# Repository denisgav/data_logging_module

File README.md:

Board connects SD Card, RTC and BME sensors.
Can be used to measeure temperature, hummidity and pressure.
SD card can be used to lod the data.

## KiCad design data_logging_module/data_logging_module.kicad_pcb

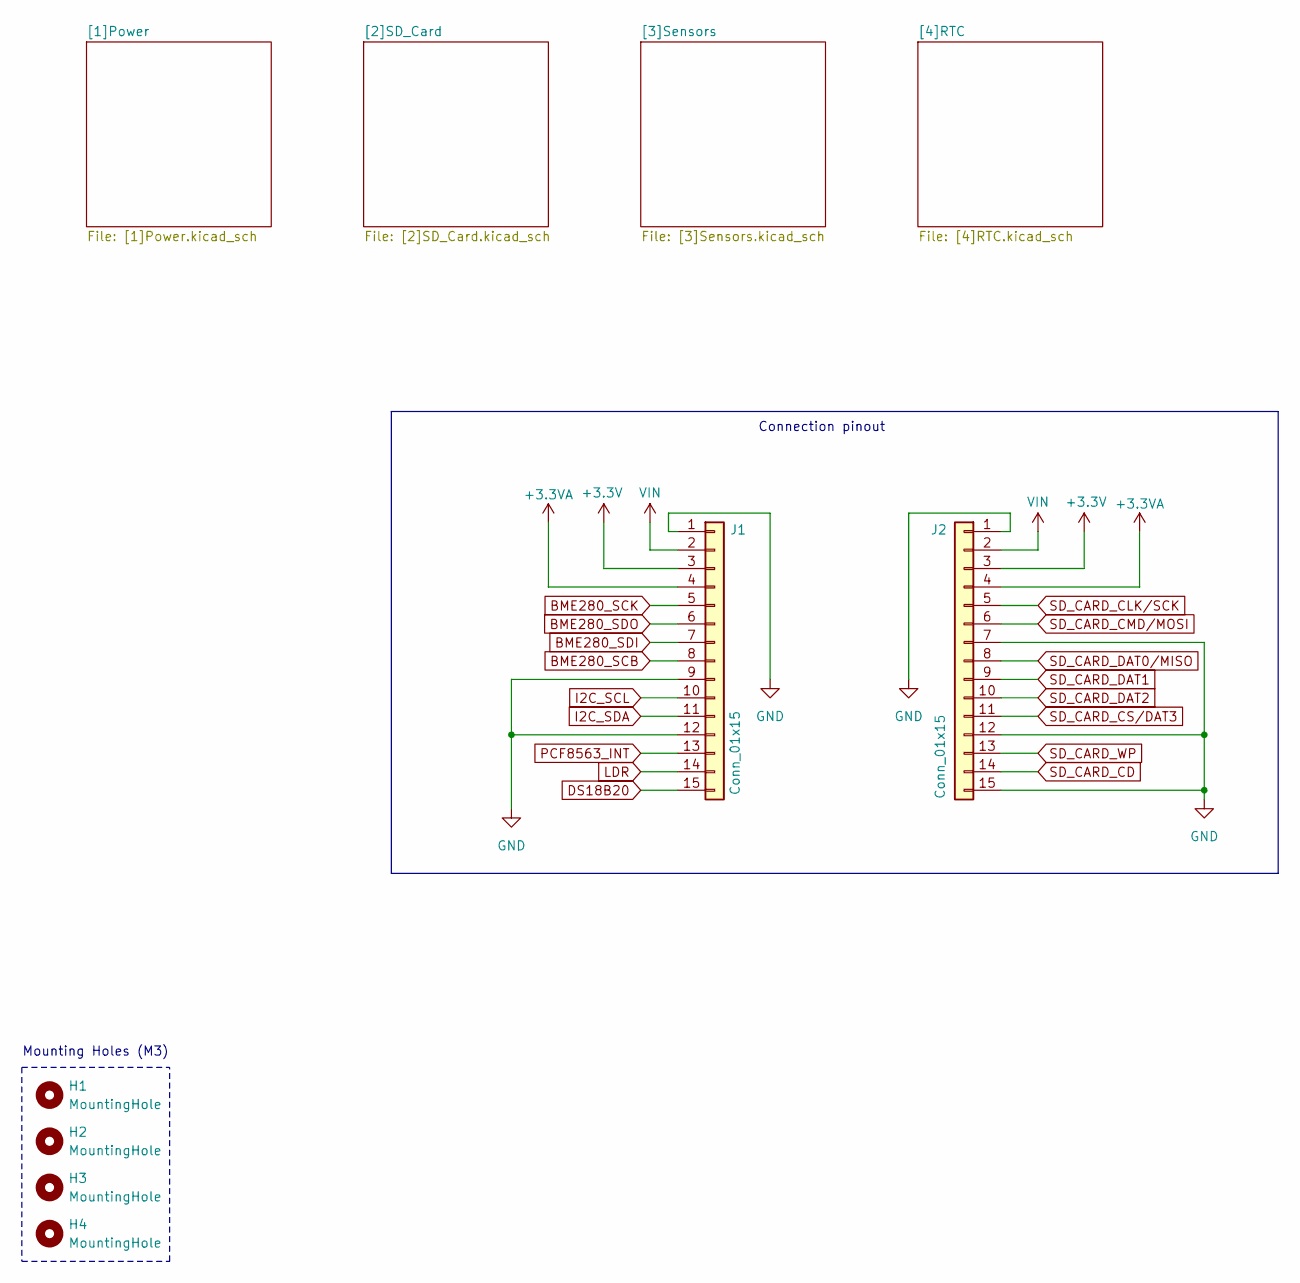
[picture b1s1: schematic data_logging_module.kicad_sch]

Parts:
H1, H2, H3, H4: MountingHole; MountingHole_3.2mm_M3
J1, J2: Conn_01x15; PinSocket_1x15_P2.54mm_Vertical

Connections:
+3.3V: J1.3, J2.3; also elsewhere on the board
+3.3VA: J1.4, J2.4; also elsewhere on the board
BME280_SCB: J1.8; also elsewhere on the board
BME280_SCK: J1.5; also elsewhere on the board
BME280_SDI: J1.7; also elsewhere on the board
BME280_SDO: J1.6; also elsewhere on the board
DS18B20: J1.15; also elsewhere on the board
GND: J1.1, J1.9, J1.12, J2.1, J2.7, J2.12, J2.15; also elsewhere on the board
I2C_SCL: J1.10; also elsewhere on the board
I2C_SDA: J1.11; also elsewhere on the board
LDR: J1.14; also elsewhere on the board
PCF8563_INT: J1.13; also elsewhere on the board
SD_CARD_CD: J2.14; also elsewhere on the board
SD_CARD_CLK/SCK: J2.5; also elsewhere on the board
SD_CARD_CMD/MOSI: J2.6; also elsewhere on the board
SD_CARD_CS/DAT3: J2.11; also elsewhere on the board
SD_CARD_DAT0/MISO: J2.8; also elsewhere on the board
SD_CARD_DAT1: J2.9; also elsewhere on the board
SD_CARD_DAT2: J2.10; also elsewhere on the board
SD_CARD_WP: J2.13; also elsewhere on the board
VIN: J1.2, J2.2; also elsewhere on the board

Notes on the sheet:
Mounting Holes (M3)
Connection pinout

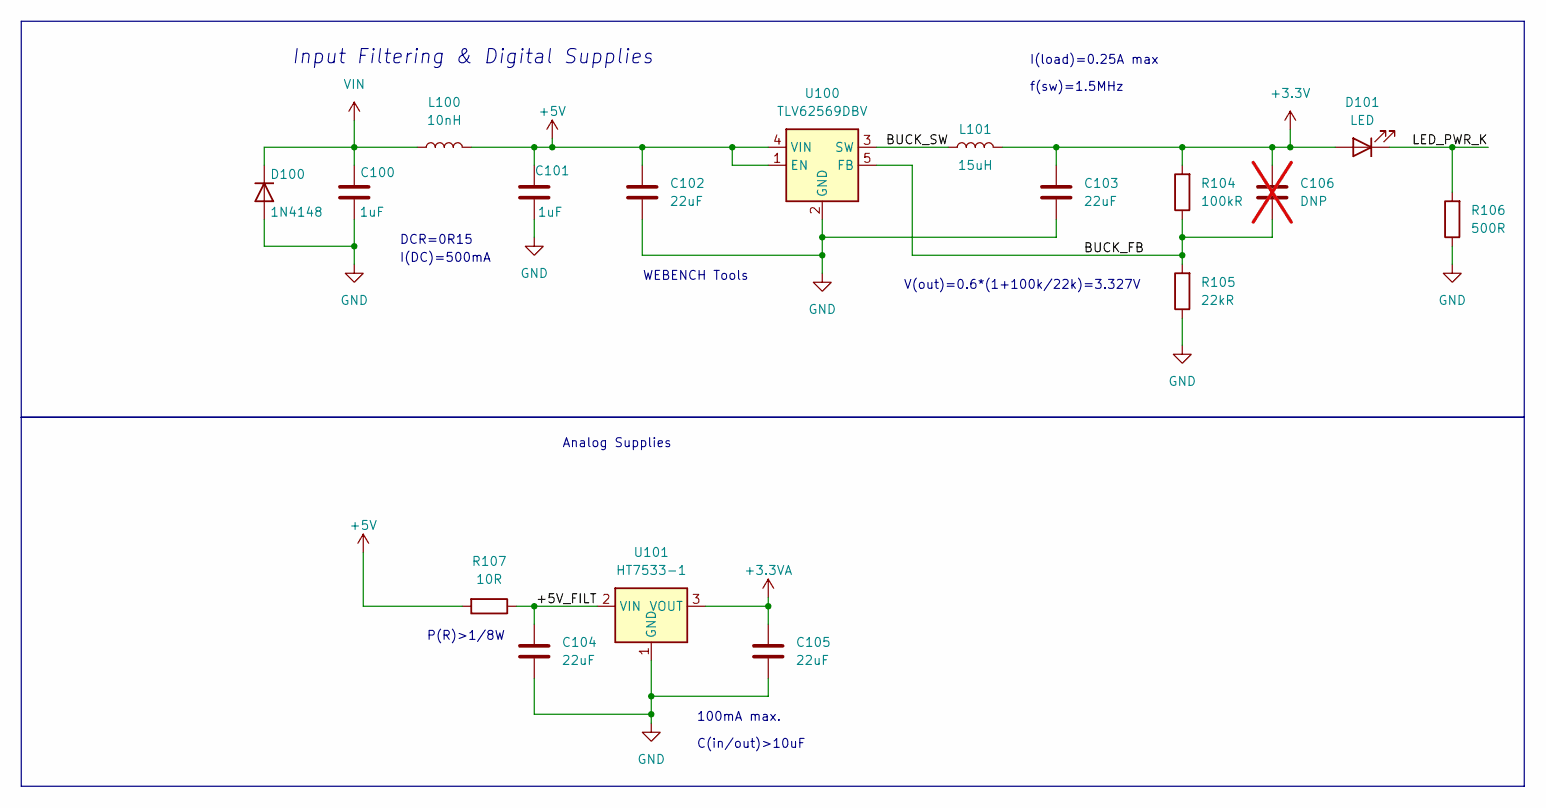
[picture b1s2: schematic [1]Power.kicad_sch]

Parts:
C100, C101: 1uF; C_0805_2012Metric; Manufacturer Part Number CL21B105KBFNNNE; DigiKey Part Number 1276-1946-6-ND
C102, C103: 22uF; C_0805_2012Metric; Manufacturer Part Number CL21A226MAYNNNE; DigiKey Part Number 1276-6687-6-ND
C104, C105: 22uF; C_0805_2012Metric; Manufacturer Part Number CL21A226MAYNNNE
C106: DNP; C_0603_1608Metric; not fitted
D100: 1N4148; D_SOD-123; Manufacturer Part Number 1N4148W
D101: LED; LED_D5.0mm; DigiKey Part Number 732-4971-6-ND
L100: 10nH; L_0603_1608Metric; Manufacturer Part Number LQG18HN10NJ00D; DigiKey Part Number 712-LRC0402CJ10NGV001TDKR-ND
L101: 15uH; MWSA0603S; Manufacturer Part Number FXL0630-150-M; DigiKey Part Number 3442-MWSA0603S-150MTDKR-ND
R104: 100kR; R_0805_2012Metric; Manufacturer Part Number 0805W8F1003T5E; DigiKey Part Number P100KLDKR-ND
R105: 22kR; R_0805_2012Metric; Manufacturer Part Number 0805W8F2202T5E; DigiKey Part Number P22.0KLDKR-ND
R106: 500R; R_0805_2012Metric; Manufacturer Part Number ARG05FTC5000; DigiKey Part Number P1.00KLDKR-ND
R107: 10R; R_0805_2012Metric; Manufacturer Part Number 0805W8F100JT5E
U100: TLV62569DBV; SOT-23-5; Manufacturer Part Number TLV62569DBVR; DigiKey Part Number 296-47360-6-ND
U101: HT7533-1; SOT-89-3; Manufacturer Part Number HT7533-1

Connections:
+3.3V: C103.1, C106.1, D101.2 (A), L101.2, R104.2; also elsewhere on the board
+3.3VA: C105.1, U101.3 (VOUT); also elsewhere on the board
+5V: C101.1, C102.1, L100.2, R107.2, U100.1 (EN), U100.4 (VIN)
/[1]Power/+5V_FILT: C104.1, R107.1, U101.2 (VIN)
/[1]Power/BUCK_FB: C106.2, R104.1, R105.2, U100.5 (FB)
/[1]Power/BUCK_SW: L101.1, U100.3 (SW)
/[1]Power/LED_PWR_K: D101.1 (K), R106.2
GND: C100.2, C101.2, C102.2, C103.2, C104.2, C105.2, D100.2 (A), R105.1, R106.1, U100.2 (GND), U101.1 (GND); also elsewhere on the board
VIN: C100.1, D100.1 (K), L100.1; also elsewhere on the board

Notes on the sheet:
Input Filtering & Digital Supplies
V(out)=0.6*(1+100k/22k)=3.327V
I(DC)=500mA
Analog Supplies
WEBENCH Tools
100mA max.
I(load)=0.25A max
P(R)>1/8W
DCR=0R15
C(in/out)>10uF
f(sw)=1.5MHz

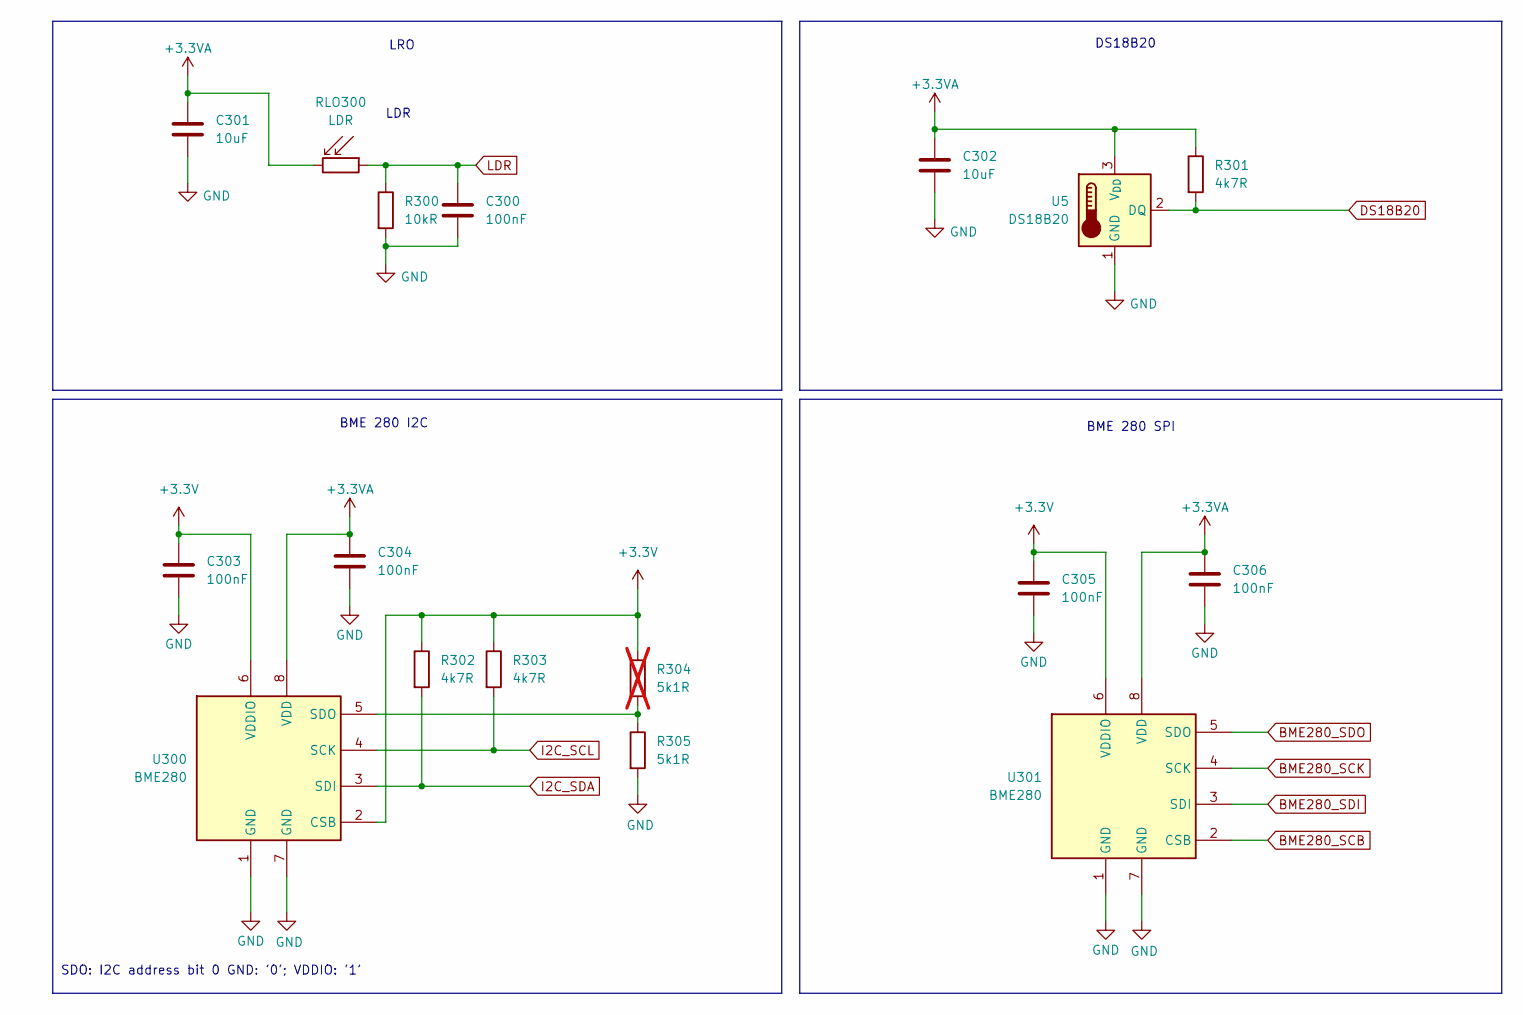
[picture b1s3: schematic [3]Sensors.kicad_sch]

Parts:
C300, C303, C304, C305, C306: 100nF; C_0603_1608Metric; Manufacturer Part Number CL10B104KB8NNNC
C301, C302: 10uF; C_0805_2012Metric; Manufacturer Part Number CL21A106KOQNNNE
R300: 10kR; R_0805_2012Metric; Manufacturer Part Number 0805W8F1002T5E
R301, R302, R303: 4k7R; R_0805_2012Metric; Manufacturer Part Number 0805W8F4701T5E
R304: 5k1R; R_0805_2012Metric; Manufacturer Part Number 0805W8F5101T5E; not fitted
R305: 5k1R; R_0805_2012Metric; Manufacturer Part Number 0805W8F5101T5E
RLO300: LDR; R_LDR_5.1x4.3mm_P3.4mm_Vertical; Manufacturer Part Number GL5528(10-20)
U5: DS18B20; TO-92_Inline; Manufacturer Part Number DS18B20(UMW)
U300, U301: BME280; Bosch_LGA-8_2.5x2.5mm_P0.65mm_ClockwisePinNumbering; Manufacturer Part Number BME280

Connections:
+3.3V: C303.1, C305.1, R302.1, R303.1, R304.1, U300.2 (CSB), U300.6 (VDDIO), U301.6 (VDDIO); also elsewhere on the board
+3.3VA: C301.1, C302.1, C304.1, C306.1, R301.1, RLO300.2, U5.3 (V_{DD}), U300.8 (VDD), U301.8 (VDD); also elsewhere on the board
BME280_SCB: U301.2 (CSB); also elsewhere on the board
BME280_SCK: U301.4 (SCK); also elsewhere on the board
BME280_SDI: U301.3 (SDI); also elsewhere on the board
BME280_SDO: U301.5 (SDO); also elsewhere on the board
DS18B20: R301.2, U5.2 (DQ); also elsewhere on the board
GND: C300.2, C301.2, C302.2, C303.2, C304.2, C305.2, C306.2, R300.2, R305.2, U5.1 (GND), U300.1 (GND), U300.7 (GND), U301.1 (GND), U301.7 (GND); also elsewhere on the board
I2C_SCL: R303.2, U300.4 (SCK); also elsewhere on the board
I2C_SDA: R302.2, U300.3 (SDI); also elsewhere on the board
LDR: C300.1, R300.1, RLO300.1; also elsewhere on the board
unnamed: R304.2, R305.1, U300.5 (SDO)

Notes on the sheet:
LRO
DS18B20
BME 280 SPI
BME 280 I2C
LDR
SDO: I2C address bit 0 GND: '0'; VDDIO: '1'

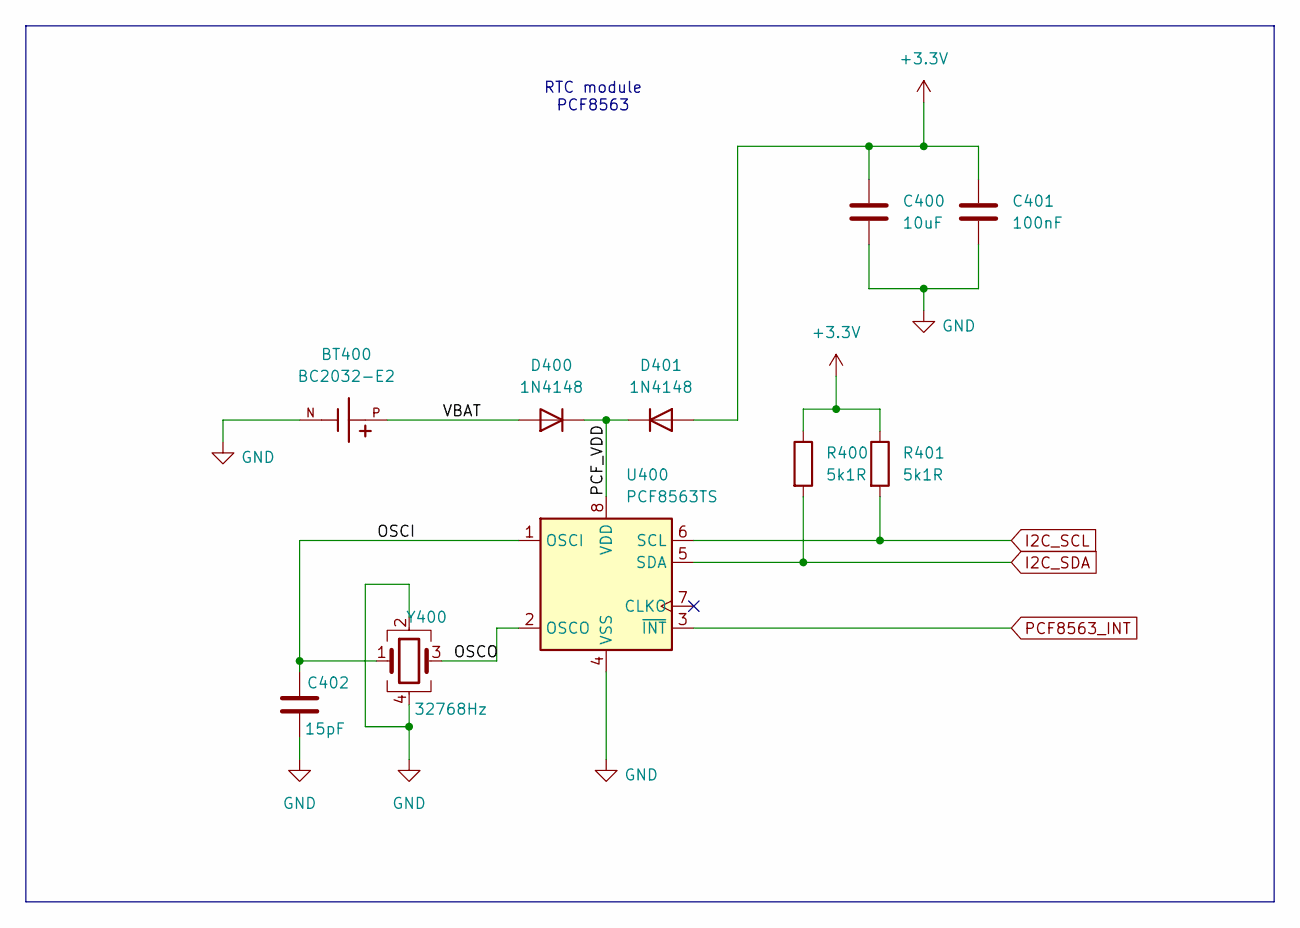
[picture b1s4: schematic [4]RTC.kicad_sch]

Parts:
BT400: BC2032-E2; MPD_BC2032-E2; PARTREV D
C400: 10uF; C_0805_2012Metric; Manufacturer Part Number CL21A106KOQNNNE
C401: 100nF; C_0603_1608Metric; Manufacturer Part Number CL10B104KB8NNNC
C402: 15pF; C_0603_1608Metric; Manufacturer Part Number CL10C150JB8NNNC; DigiKey Part Number 490-11191-6-ND
D400, D401: 1N4148; D_SOD-123; Manufacturer Part Number 1N4148W
R400, R401: 5k1R; R_0805_2012Metric; Manufacturer Part Number 0805W8F5101T5E
U400: PCF8563TS; MSOP-8_3x3mm_P0.65mm; Manufacturer Part Number PCF8563TS/5,118
Y400: 32768Hz; Crystal_SMD_3225-4Pin_3.2x2.5mm; Manufacturer Part Number OK2EL89CJI-111YLC-32.768K; DigiKey Part Number 535-ASEK-32.768KHZ-L-R-TDKR-ND

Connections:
+3.3V: C400.1, C401.1, D401.2 (A), R400.1, R401.1; also elsewhere on the board
/[4]RTC/OSCI: C402.1, U400.1 (OSCI), Y400.1
/[4]RTC/OSCO: U400.2 (OSCO), Y400.3
/[4]RTC/PCF_VDD: D400.1 (K), D401.1 (K), U400.8 (VDD)
/[4]RTC/VBAT: BT400.P, D400.2 (A)
GND: BT400.N, C400.2, C401.2, C402.2, U400.4 (VSS), Y400.2, Y400.4; also elsewhere on the board
I2C_SCL: R401.2, U400.6 (SCL); also elsewhere on the board
I2C_SDA: R400.2, U400.5 (SDA); also elsewhere on the board
PCF8563_INT: U400.3 (~INT); also elsewhere on the board

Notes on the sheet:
RTC module PCF8563

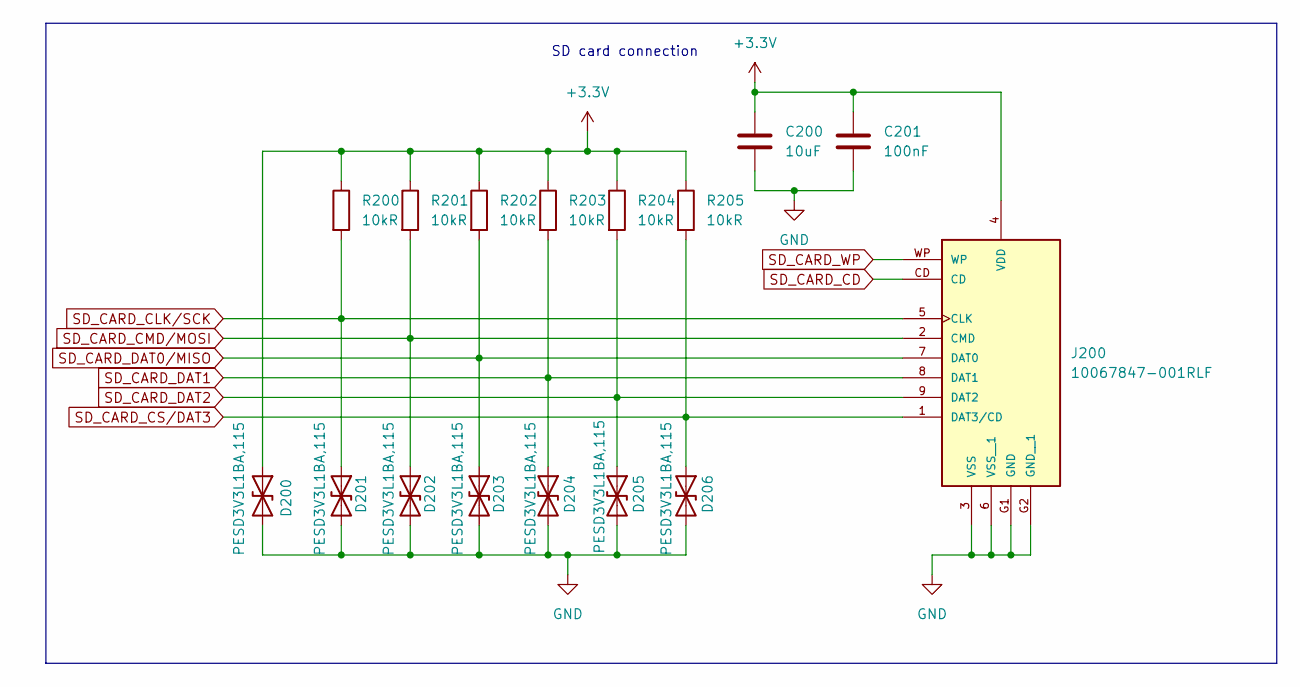
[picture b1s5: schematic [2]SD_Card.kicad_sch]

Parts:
C200: 10uF; C_0805_2012Metric; Manufacturer Part Number CL21A106KOQNNNE
C201: 100nF; C_0603_1608Metric; Manufacturer Part Number CL10B104KB8NNNC
D200, D201, D202, D203, D204, D205, D206: PESD3V3L1BA,115; D_SOD-323; Manufacturer Part Number PESD3V3L1BA,115; DigiKey Part Number 1727-3825-6-ND
J200: 10067847-001RLF; AMPHENOL_10067847-001RLF; PARTREV K
R200, R201, R202, R203, R204, R205: 10kR; R_0805_2012Metric; Manufacturer Part Number 0805W8F1002T5E

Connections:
+3.3V: C200.1, C201.1, D200.1 (A1), J200.4 (VDD), R200.1, R201.1, R202.1, R203.1, R204.1, R205.1; also elsewhere on the board
GND: C200.2, C201.2, D200.2 (A2), D201.2 (A2), D202.2 (A2), D203.2 (A2), D204.2 (A2), D205.2 (A2), D206.2 (A2), J200.3 (VSS), J200.6 (VSS__1), J200.G1 (GND), J200.G2 (GND__1); also elsewhere on the board
SD_CARD_CD: J200.CD; also elsewhere on the board
SD_CARD_CLK/SCK: D201.1 (A1), J200.5 (CLK), R200.2; also elsewhere on the board
SD_CARD_CMD/MOSI: D202.1 (A1), J200.2 (CMD), R201.2; also elsewhere on the board
SD_CARD_CS/DAT3: D206.1 (A1), J200.1 (DAT3/CD), R205.2; also elsewhere on the board
SD_CARD_DAT0/MISO: D203.1 (A1), J200.7 (DAT0), R202.2; also elsewhere on the board
SD_CARD_DAT1: D204.1 (A1), J200.8 (DAT1), R203.2; also elsewhere on the board
SD_CARD_DAT2: D205.1 (A1), J200.9 (DAT2), R204.2; also elsewhere on the board
SD_CARD_WP: J200.WP; also elsewhere on the board

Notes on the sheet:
SD card connection

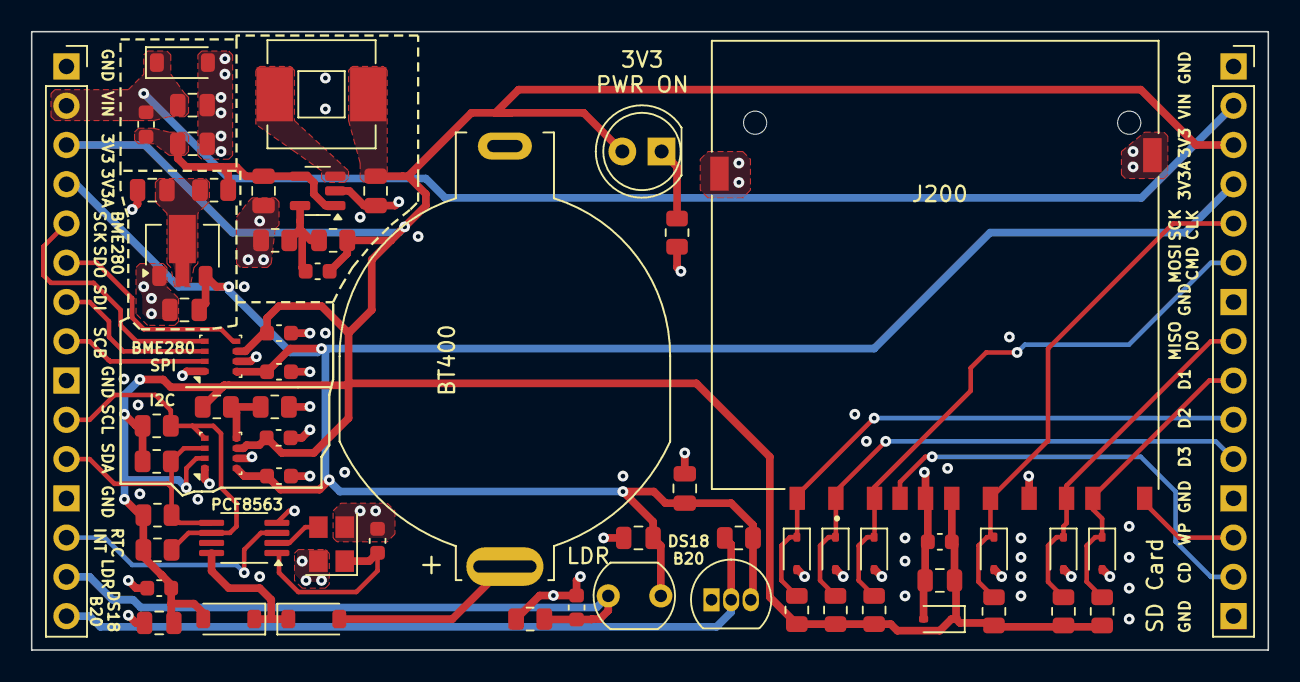
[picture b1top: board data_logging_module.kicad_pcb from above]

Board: 4 copper layers, 80.0 x 40.0 mm, 62 parts (0 on the bottom side), 31 nets.

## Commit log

2025-02-20 Initial scheme
2025-02-20 BOM updates
2025-02-21 PCB initial layout
2025-02-21 initial PCB
2025-02-22 Silkscreen updates
2025-02-22 Add scheme plots
2025-02-22 Fill front and back copper layers by ground
2025-02-24 Updates in power wiring
2025-02-24 Add decoupling capacitors to analog sensors
2025-02-25 Remove front copper mask
